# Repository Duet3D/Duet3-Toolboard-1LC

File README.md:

# Duet-3-Toolboard-1LC
Hardware information for the Duet 3 Toolboard 1LC. This is a CAN-FD connected expansion board for Duet 3 Mainboards:[Duet 3 6HC](https://www.duet3d.com/Duet3Mainboard6HC), [Duet 3 Mini 5+](https://www.duet3d.com/duet3mini5plus) or [Duet 3 6XD](https://www.duet3d.com/duet3mainboard6xd) that is designed to provide complete control for a direct drive extruder. 

Product page is here: https://www.duet3d.com/Duet3Toolboard1LC

Documentation is here: https://docs.duet3d.com/en/Duet3D_hardware/Duet_3_family/Duet_3_Toolboard_1LC

As always please discuss this on the Duet3d forum: https://forum.duet3d.com/

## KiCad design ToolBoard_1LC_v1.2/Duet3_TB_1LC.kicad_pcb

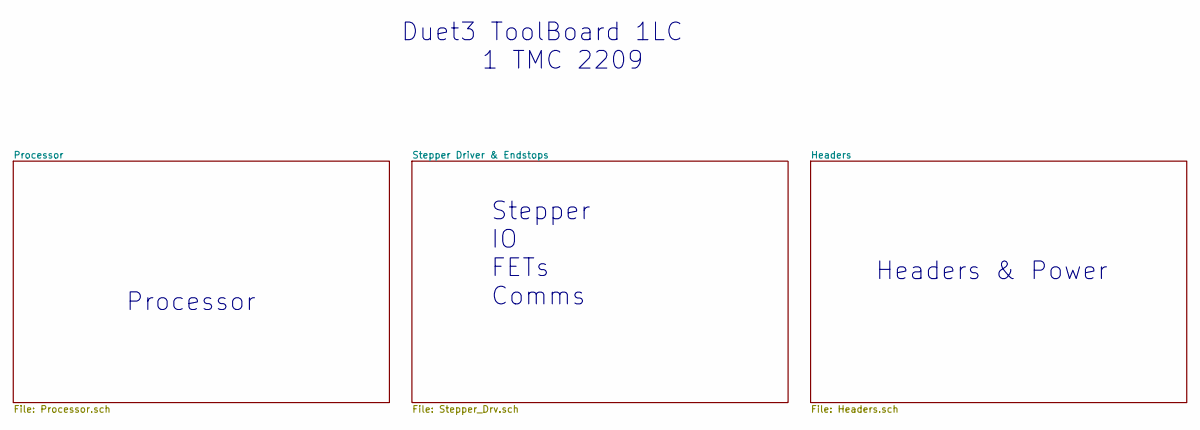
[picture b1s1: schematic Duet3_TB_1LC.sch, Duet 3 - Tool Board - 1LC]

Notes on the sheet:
Processor
Stepper IO FETs Comms
Headers & Power
Duet3 ToolBoard 1LC 1 TMC 2209

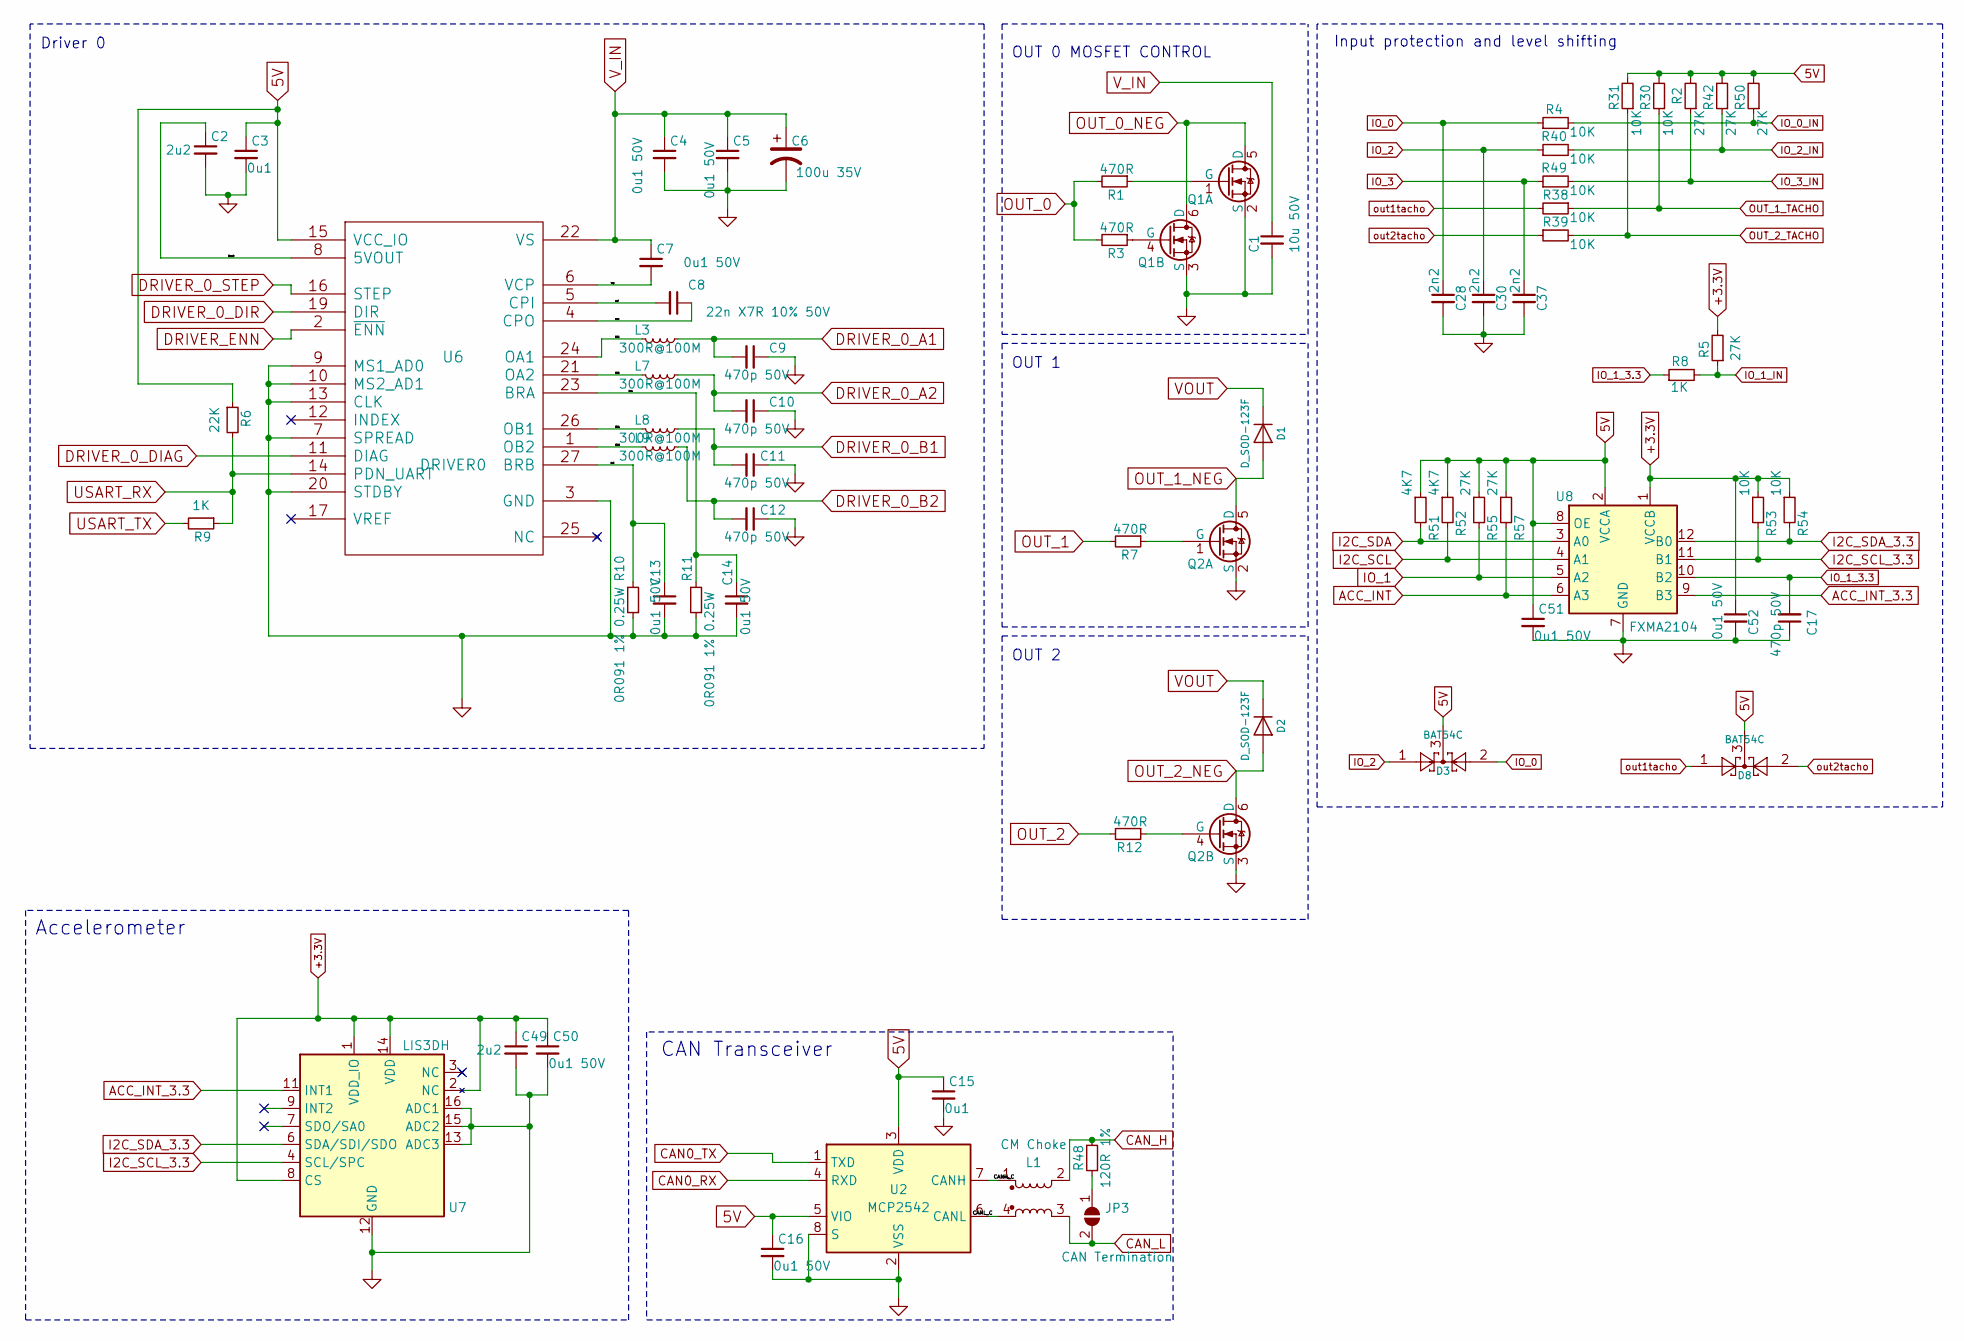
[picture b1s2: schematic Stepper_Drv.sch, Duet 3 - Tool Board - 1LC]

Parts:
C1: 10u 50V; C_1206_3216Metric; Part Number CL31A106KBHNNNE
C2, C49: 2u2; C_0603_1608Metric_Wbry; Part Number GRM188R6YA225KA12D
C3, C15: 0u1; C_0402_1005Metric_Wbry; Part Number CL05A104KA5NNNC
C4, C5, C7, C13, C14, C16, C50, C51, C52: 0u1 50V; C_0402_1005Metric_Wbry; Part Number GCM155R71H104KE02D
C6: 100u 35V; CP_Elec_6.3x7.7; Part Number 865080545012
C8: 22n X7R 10% 50V; C_0402_1005Metric_Wbry; Part Number CC0402KRX7R9BB223
C9, C10, C11, C12, C17: 470p 50V; C_0402_1005Metric_Wbry; Part Number CC0402KRX7R9BB471
C28, C30, C37: 2n2; C_0402_1005Metric_Wbry; Part Number CC0402KRX7R9BB222 or similar (10v+ is f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
D1, D2: D_SOD-123F; Part Number HS1KFL or equivalent
D3, D8: BAT54C; SOT-23; Part Number BAT54C-7-F/BAT54CLT1G
JP3: CAN Termination; SolderJumper-2_P1.3mm_Open_TrianglePad1.0x1.5mm
L1: CM Choke; Wurth_CM_Choke_744231121; Part Number 744231121 or SRF2012A-121YA
L3, L7, L8, L9: 300R@100M; L_0603_1608Metric; Part Number 742792641 or similar
Q1, Q2: Q_DUAL_NMOS; Fairchild_DualPower33-6_3x3mm-gap; Part Number DMT6018LDR
R1, R3, R7, R12: 470R; R_0402_1005Metric_Wbry; Part Number RK73H1ETTP4700F
R2, R5, R42, R50, R55, R57: 27K; R_0402_1005Metric_Wbry; Part Number RK73H1ETTP2702F
R4, R30, R31, R38, R39, R40, R49: 10K; R_0402_1005Metric_Wbry; Part Number RK73H1ETTP1002F
R6: 22K; R_0402_1005Metric_Wbry; Part Number RK73H1ETTP2202F
R8, R9: 1K; R_0402_1005Metric_Wbry; Part Number RK73H1ETTP1001F
R10, R11: 0R091 1% 0.25W; R_0402_1005Metric_Wbry; Part Number ERJ-2BWFR091X or RLP73M1ER091FTDF
R48: 120R 1%; R_0402_1005Metric_Wbry; Part Number RMCF0402FT120R
R51, R52: 4K7; R_0402_1005Metric_Wbry; Part Number RK73H1ETTP4701F
R53, R54: 10K; R_0402_1005Metric_Wbry; Part Number RK73H1ETTP4701F
U2: MCP2542; DFN-8-1EP_3x2mm_P0.5mm_EP1.3x1.5mm-thinpads; Part Number MCP2542, alternitivelty MCP2558
U6: DRIVER0; QFN-28-1EP_5x5mm_Pitch0.5mm-thinpads; Part Number TMC2209
U7: LIS3DH; Part Number LIS3DHTR
U8: FXMA2104; UMLP-12-1.8x1.8mm_P0.4mm

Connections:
5V: C3.1, C15.1, C16.1, C51.1, D3.3, D8.3, R2.2, R6.1, R30.2, R31.2, R42.2, R50.2, R51.1, R52.1, R55.1, R57.1, U2.3 (VDD), U2.5 (VIO), U6.15 (VCC_IO), U8.2 (VCCA), U8.8 (OE); also elsewhere on the board
+3.3V: C49.1, C50.1, C52.1, R5.2, R53.1, R54.1, U7.1 (VDD_IO), U7.2 (NC), U7.8 (CS), U7.14 (VDD), U8.1 (VCCB); also elsewhere on the board
/Stepper Driver & Endstops/5vout: C2.1, U6.8 (5VOUT)
/Stepper Driver & Endstops/CANH_C: L1.1, U2.7 (CANH)
/Stepper Driver & Endstops/CANL_C: L1.4, U2.6 (CANL)
/Stepper Driver & Endstops/OA1: L3.2, U6.24 (OA1)
/Stepper Driver & Endstops/OA2: L7.2, U6.21 (OA2)
/Stepper Driver & Endstops/OB1: L8.2, U6.26 (OB1)
/Stepper Driver & Endstops/OB2: L9.2, U6.1 (OB2)
/Stepper Driver & Endstops/bra: C14.1, R11.2, U6.23 (BRA)
/Stepper Driver & Endstops/brb: C13.1, R10.2, U6.27 (BRB)
/Stepper Driver & Endstops/cpi: C8.2, U6.5 (CPI)
/Stepper Driver & Endstops/cpo: C8.1, U6.4 (CPO)
/Stepper Driver & Endstops/vcp: C7.2, U6.6 (VCP)
ACC_INT: R57.2, U8.6 (A3); also elsewhere on the board
ACC_INT_3.3: U7.11 (INT1), U8.9 (B3)
CAN0_RX: U2.4 (RXD); also elsewhere on the board
CAN0_TX: U2.1 (TXD); also elsewhere on the board
CAN_H: L1.2, R48.2; also elsewhere on the board
CAN_L: JP3.2 (B), L1.3; also elsewhere on the board
DRIVER_0_A1: C9.2, L3.1; also elsewhere on the board
DRIVER_0_A2: C10.2, L7.1; also elsewhere on the board
DRIVER_0_B1: C11.2, L8.1; also elsewhere on the board
DRIVER_0_B2: C12.2, L9.1; also elsewhere on the board
DRIVER_0_DIAG: U6.11 (DIAG); also elsewhere on the board
DRIVER_0_DIR: U6.19 (DIR); also elsewhere on the board
DRIVER_0_STEP: U6.16 (STEP); also elsewhere on the board
DRIVER_ENN: U6.2 (~ENN); also elsewhere on the board
GND: C1.2, C2.2, C3.2, C4.2, C5.2, C6.2, C9.1, C10.1, C11.1, C12.1, C13.2, C14.2, C15.2, C16.2, C17.1, C28.2, C30.2, C37.2, C49.2, C50.2, C51.2, C52.2, Q1.2 (S), Q1.3 (S), Q2.2 (S), Q2.3 (S), R10.1, R11.1, U2.2 (VSS), U2.8 (S), U2.9 (VSS), U6.3 (GND), U6.7 (SPREAD), U6.9 (MS1_AD0), U6.10 (MS2_AD1), U6.13 (CLK), U6.18 (GND), U6.20 (STDBY), U6.29 (GND), U7.5 (GND), U7.10 (GND), U7.12 (GND), U7.13 (ADC3), U7.15 (ADC2), U7.16 (ADC1), U8.7 (GND); also elsewhere on the board
I2C_SCL: R52.2, U8.4 (A1); also elsewhere on the board
I2C_SCL_3.3: R53.2, U7.4 (SCL/SPC), U8.11 (B1)
I2C_SDA: R51.2, U8.3 (A0); also elsewhere on the board
I2C_SDA_3.3: R54.2, U7.6 (SDA/SDI/SDO), U8.12 (B0)
IO_0: C28.1, D3.2, R4.1; also elsewhere on the board
IO_0_IN: R4.2, R50.1; also elsewhere on the board
IO_1: R55.2, U8.5 (A2); also elsewhere on the board
IO_1_3.3: C17.2, R8.1, U8.10 (B2)
IO_1_IN: R5.1, R8.2; also elsewhere on the board
IO_2: C30.1, D3.1, R40.1; also elsewhere on the board
IO_2_IN: R40.2, R42.1; also elsewhere on the board
IO_3: C37.1, R49.1; also elsewhere on the board
IO_3_IN: R2.1, R49.2; also elsewhere on the board
unnamed: JP3.1 (A), R48.1
unnamed: Q1.1 (G), R1.1
unnamed: Q1.4 (G), R3.1
unnamed: Q2.1 (G), R7.1
unnamed: Q2.4 (G), R12.1
OUT_0: R1.2, R3.2; also elsewhere on the board
OUT_0_NEG: Q1.5 (D), Q1.6 (D); also elsewhere on the board
OUT_1: R7.2; also elsewhere on the board
OUT_1_NEG: D1.2 (A), Q2.5 (D); also elsewhere on the board
OUT_1_TACHO: R30.1, R38.1; also elsewhere on the board
OUT_2: R12.2; also elsewhere on the board
OUT_2_NEG: D2.2 (A), Q2.6 (D); also elsewhere on the board
OUT_2_TACHO: R31.1, R39.2; also elsewhere on the board
USART_RX: R6.2, R9.1, U6.14 (PDN_UART); also elsewhere on the board
USART_TX: R9.2; also elsewhere on the board
VOUT: D1.1 (K), D2.1 (K); also elsewhere on the board
V_IN: C1.1, C4.1, C5.1, C6.1, C7.1, U6.22 (VS), U6.28 (VS); also elsewhere on the board
out1tacho: D8.1, R38.2; also elsewhere on the board
out2tacho: D8.2, R39.1; also elsewhere on the board

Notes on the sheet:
Input protection and level shifting
Driver 0
OUT 1
OUT 0 MOSFET CONTROL
CAN Transceiver
OUT 2
Accelerometer

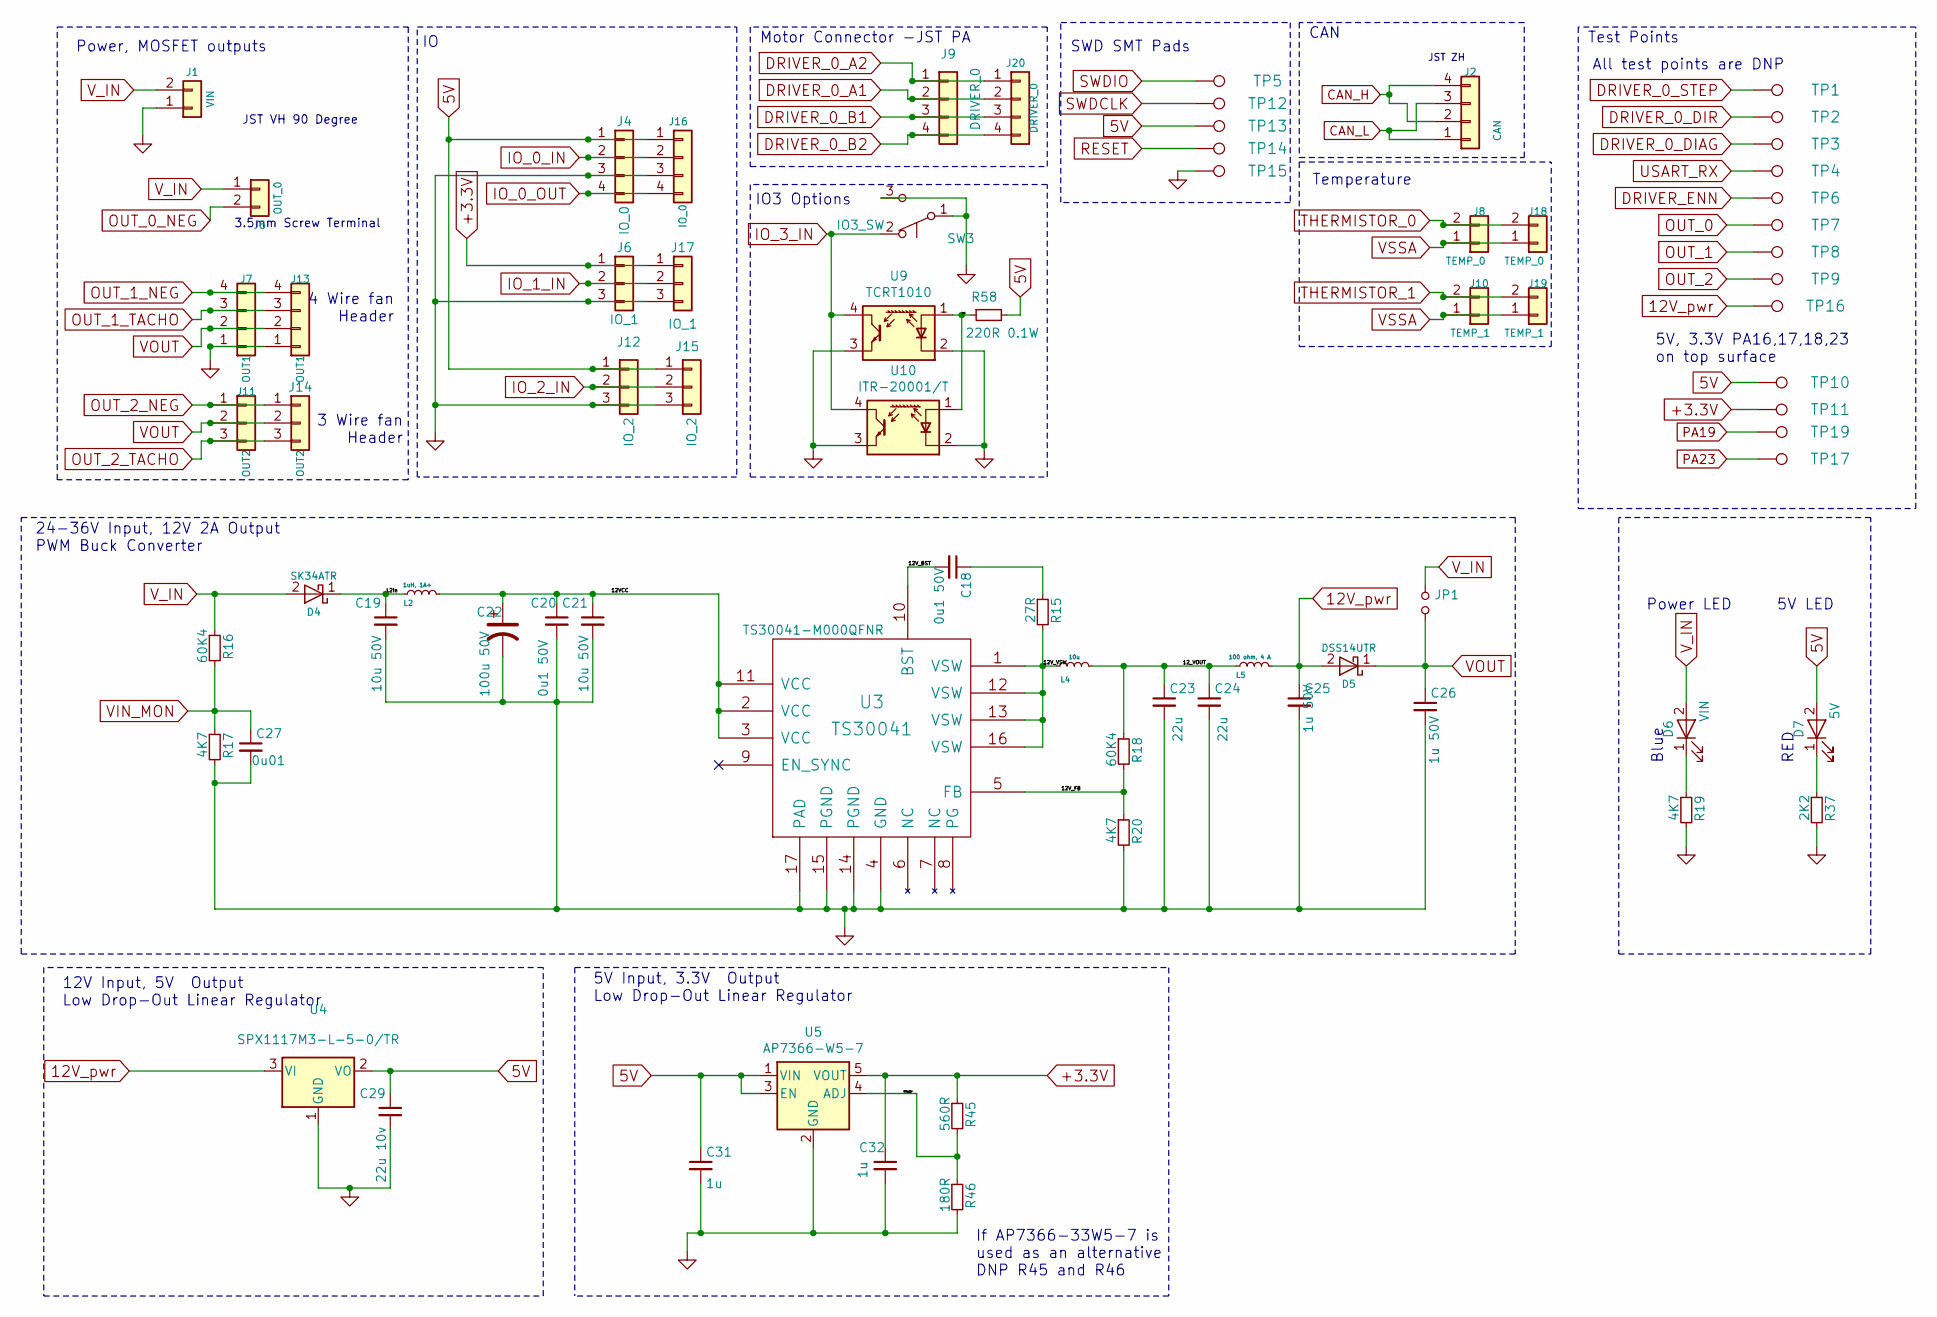
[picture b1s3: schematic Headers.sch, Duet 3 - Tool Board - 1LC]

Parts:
C18: 0u1 50V; C_0402_1005Metric_Wbry; Part Number CL05A104KA5NNNC
C19, C21: 10u 50V; C_1206_3216Metric; Part Number CL31A106KBHNNNE
C20: 0u1 50V; C_0402_1005Metric_Wbry; Part Number GRM155R61H104JE14D
C22: 100u 50V; CP_Elec_6.3x7.7; Part Number EEE-FTH101XAP
C23, C24: 22u; C_0805_2012Metric; Rating 25V; Part Number GRM21BR61E226ME44L
C25, C26: 1u 50V; C_0603_1608Metric_Wbry; Part Number CL10A105KB8NNNC
C27: 0u01; C_0402_1005Metric_Wbry; Part Number TMK105B7103KV-F
C29: 22u 10v; C_0805_2012Metric; Part Number GRM21BR61A226ME51L or equivalent
C31, C32: 1u; C_0603_1608Metric_Wbry; Part Number CL10A105KA8NNNC
D4: SK34ATR; D_SMA; Rating 1A+ 40V+; Part Number SK34ATR or similar SMA footprint
D5: DSS14UTR; D_SOD-123F; Rating 1A,40V; Part Number DSS14UTR or RB162MM-40TR or similar
D6: VIN; LED_0603_1608Metric; Part Number 150060BS75000 or equivalent Blue
D7: 5V; LED_0603_1608Metric; Part Number 150060RS75000 or equivalent Red
J1: VIN; JST_VH_B2PS-VH_1x02_P3.96mm_Short_Horizontal; Part Number B2PS-VH(LF)(SN)
J2: CAN; JST_ZH_S4B-ZH_1x04_P1.50mm_Horizontal; Part Number S4B-ZR(LF)(SN)
J4: IO_0; JST_PH_S4B-PH-K_1x04_P2.00mm_Horizontal; Part Number S4B-PH-K-S(LF)(SN)
J5: OUT_0; 3.5MM_2X1; Part Number Kaifeng KF128L-3.50-2
J6: IO_1; JST_PH_S3B-PH-K_1x03_P2.00mm_Horizontal; Part Number S3B-PH-K-S(LF)(SN)
J7: OUT1; JST_PH_S4B-PH-K_1x04_P2.00mm_Horizontal; Part Number S4B-PH-K-S(LF)(SN)
J8: TEMP_0; JST_PH_S2B-PH-K_1x02_P2.00mm_Horizontal; Part Number S2B-PH-K-S(LF)(SN)
J9: DRIVER_0; JST_PH_S4B-PH-K_1x04_P2.00mm_Horizontal; Part Number S4B-PH-K-S(LF)(SN)
J10: TEMP_1; JST_PH_S2B-PH-K_1x02_P2.00mm_Horizontal; Part Number S2B-PH-K-S(LF)(SN)
J11: OUT2; JST_PH_S3B-PH-K_1x03_P2.00mm_Horizontal; Part Number S3B-PH-K-S(LF)(SN)
J12: IO_2; JST_PH_S3B-PH-K_1x03_P2.00mm_Horizontal; Part Number S3B-PH-K-S(LF)(SN)
J13: OUT1; TerminalBlock_TE_282834-4_1x04_P2.54mm_Horizontal; Part Number - DNP
J14: OUT2; TerminalBlock_TE_282834-3_1x03_P2.54mm_Horizontal; Part Number - DNP
J15: IO_2; TerminalBlock_TE_282834-3_1x03_P2.54mm_Horizontal; Part Number DNP
J16: IO_0; TerminalBlock_TE_282834-4_1x04_P2.54mm_Horizontal; Part Number - DNP
J17: IO_1; TerminalBlock_TE_282834-3_1x03_P2.54mm_Horizontal; Part Number - DNP
J18: TEMP_0; TerminalBlock_Valcon_MB312-2.54-02_P2.54mm_Horizontal; Part Number MB312-2.54-02_P2.54mm - DNP
J19: TEMP_1; TerminalBlock_Valcon_MB312-2.54-02_P2.54mm_Horizontal; Part Number MB312-2.54-02_P2.54mm - DNP
J20: DRIVER_0; TerminalBlock_TE_282834-4_1x04_P2.54mm_Horizontal; Part Number - DNP
JP1: V_OUT JMP; PinHeader_1x02_P2.54mm_Vertical
L2: 1uH, 1A+; L_1008_2512Metric; Part Number MGV2520101R0M-10 or similar 1008 footpr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
L4: 10u; L_Wuerth_7440405xxxx; Part Number 74404054100 or NR5040T100M
L5: 100 ohm, 4 A; L_0805_2012Metric; Part Number MPZ2012S101A or similar
R15: 27R; R_0402_1005Metric_Wbry; Rating 0.1W+; Part Number RC0402FR-0727RL
R16, R18: 60K4; R_0402_1005Metric_Wbry; Part Number ERJ-2RKF6042X
R17, R19, R20: 4K7; R_0402_1005Metric_Wbry; Part Number RK73H1ETTP4701F
R37: 2K2; R_0402_1005Metric_Wbry; Part Number RK73H1ETTP2201F
R45: 560R; R_0402_1005Metric_Wbry; Part Number RMCF0402FT560R
R46: 180R; R_0402_1005Metric_Wbry; Part Number RMCF0402FT180R
R58: 220R 0.1W; R_0402_1005Metric_Wbry; Part Number RK73H1ETTP2200F
SW3: IO3_SW; Ultra_Subminiature_Switch-SPDT; Part Number DNP - Omron D2FD-1L30-1T
TP1: STEP; TestPoint_Pad_D1.5mm; Part Number virtual component - DNP
TP2: DIR; TestPoint_Pad_D1.5mm; Part Number virtual component - DNP
TP3: DIAG; TestPoint_Pad_D1.5mm; Part Number virtual component - DNP
TP4: U_RX; TestPoint_Pad_D1.5mm; Part Number virtual component - DNP
TP5: SWDIO; TestPoint_Pad_D1.5mm; Part Number virtual component - DNP
TP6: ENN; TestPoint_Pad_D1.5mm; Part Number virtual component - DNP
TP7: OUT_0; TestPoint_Pad_D1.5mm; Part Number virtual component - DNP
TP8: OUT_1; TestPoint_Pad_D1.5mm; Part Number virtual component - DNP
TP9: OUT_2; TestPoint_Pad_D1.5mm; Part Number virtual component - DNP
TP10, TP13: 5V; TestPoint_Pad_D1.5mm; Part Number virtual component - DNP
TP11: 3.3V; TestPoint_Pad_D1.5mm; Part Number virtual component - DNP
TP12: SWDCLK; TestPoint_Pad_D1.5mm; Part Number virtual component - DNP
TP14: RESET; TestPoint_Pad_D1.5mm; Part Number virtual component - DNP
TP15: GND; TestPoint_Pad_D1.5mm; Part Number virtual component - DNP
TP16: 12V_pwr; TestPoint_Pad_D1.5mm; Part Number virtual component - DNP
TP17: PA23; TestPoint_Pad_D1.5mm; Part Number virtual component - DNP
TP19: PA19; TestPoint_Pad_D1.5mm; Part Number virtual component - DNP
U3: TS30041; QFN-16-1EP_3x3mm_P0.5mm_EP1.8x1.8mm-thinpads; Rating Adj (set to 12V) 1A; Part Number TS30041-M000QFNR
U4: SPX1117M3-L-5-0/TR; SOT-223-3_TabPin2; Part Number SPX1117M3-L-5-0/TR
U5: AP7366-W5-7; SOT-23-5; Part Number AP7366-W5-7 (If AP7366-33W5-7 is used a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
U9: TCRT1010; Vishay_TCRT1010; Part Number DNP
U10: ITR-20001/T; ITR-20001_T; Part Number DNP

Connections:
5V: C29.1, C31.1, D7.2 (A), J4.1, J12.1, J15.1, J16.1, R58.2, TP10.1, TP13.1, U4.2 (VO), U5.1 (VIN), U5.3 (EN); also elsewhere on the board
12V_pwr: C25.1, D5.2 (A), L5.2, TP16.1, U4.3 (VI)
+3.3V: C32.1, J6.1, J17.1, R45.1, TP11.1, U5.5 (VOUT); also elsewhere on the board
/Headers/3V3_ADJ: R45.2, R46.1, U5.4 (ADJ)
/Headers/12VCC: C20.1, C21.1, C22.1, L2.2, U3.2 (VCC), U3.3 (VCC), U3.11 (VCC)
/Headers/12V_BST: C18.2, U3.10 (BST)
/Headers/12V_FB: R18.2, R20.1, U3.5 (FB)
/Headers/12V_VSW: L4.1, R15.2, U3.1 (VSW), U3.12 (VSW), U3.13 (VSW), U3.16 (VSW)
/Headers/12_VOUT: C23.1, C24.1, L4.2, L5.1, R18.1
/Headers/L2in: C19.1, D4.1 (K), L2.1
/Headers/col: R58.1, U9.1 (A), U10.1 (A)
CAN_H: J2.2, J2.4; also elsewhere on the board
CAN_L: J2.1, J2.3; also elsewhere on the board
DRIVER_0_A1: J9.2, J20.2; also elsewhere on the board
DRIVER_0_A2: J9.1, J20.1; also elsewhere on the board
DRIVER_0_B1: J9.3, J20.3; also elsewhere on the board
DRIVER_0_B2: J9.4, J20.4; also elsewhere on the board
DRIVER_0_DIAG: TP3.1; also elsewhere on the board
DRIVER_0_DIR: TP2.1; also elsewhere on the board
DRIVER_0_STEP: TP1.1; also elsewhere on the board
DRIVER_ENN: TP6.1; also elsewhere on the board
GND: C19.2, C20.2, C21.2, C22.2, C23.2, C24.2, C25.2, C26.2, C27.2, C29.2, C31.2, C32.2, J1.1, J4.3, J6.3, J7.1, J12.3, J13.1, J15.3, J16.3, J17.3, R17.2, R19.2, R20.2, R37.2, R46.2, SW3.1 (B), SW3.3 (C), TP15.1, U3.4 (GND), U3.14 (PGND), U3.15 (PGND), U3.17 (PAD), U4.1 (GND), U5.2 (GND), U9.2 (K), U9.3 (E), U10.2 (K), U10.3 (E); also elsewhere on the board
IO_0_IN: J4.2, J16.2; also elsewhere on the board
IO_0_OUT: J4.4, J16.4; also elsewhere on the board
IO_1_IN: J6.2, J17.2; also elsewhere on the board
IO_2_IN: J12.2, J15.2; also elsewhere on the board
IO_3_IN: SW3.2 (A), U9.4 (C), U10.4 (C); also elsewhere on the board
unnamed: C18.1, R15.1
unnamed: D6.1 (K), R19.1
unnamed: D7.1 (K), R37.1
OUT_0: TP7.1; also elsewhere on the board
OUT_0_NEG: J5.2; also elsewhere on the board
OUT_1: TP8.1; also elsewhere on the board
OUT_1_NEG: J7.4, J13.4; also elsewhere on the board
OUT_1_TACHO: J7.3, J13.3; also elsewhere on the board
OUT_2: TP9.1; also elsewhere on the board
OUT_2_NEG: J11.1, J14.1; also elsewhere on the board
OUT_2_TACHO: J11.3, J14.3; also elsewhere on the board
PA19: TP19.1; also elsewhere on the board
PA23: TP17.1; also elsewhere on the board
RESET: TP14.1; also elsewhere on the board
SWDCLK: TP12.1; also elsewhere on the board
SWDIO: TP5.1; also elsewhere on the board
THERMISTOR_0: J8.2, J18.2; also elsewhere on the board
THERMISTOR_1: J10.2, J19.2; also elsewhere on the board
USART_RX: TP4.1; also elsewhere on the board
VIN_MON: C27.1, R16.2, R17.1; also elsewhere on the board
VOUT: C26.1, D5.1 (K), J7.2, J11.2, J13.2, J14.2, JP1.2; also elsewhere on the board
VSSA: J8.1, J10.1, J18.1, J19.1; also elsewhere on the board
V_IN: D4.2 (A), D6.2 (A), J1.2, J5.1, JP1.1, R16.1; also elsewhere on the board

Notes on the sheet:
Power, MOSFET outputs
Temperature
Motor Connector -JST PA
Test Points
All test points are DNP
CAN
SWD SMT Pads
4 Wire fan Header
5V, 3.3V PA16,17,18,23 on top surface
5V Input, 3.3V Output Low Drop-Out Linear Regulator
Power LED
Blue
12V Input, 5V Output Low Drop-Out Linear Regulator
24-36V Input, 12V 2A Output PWM Buck Converter
3.5mm Screw Terminal
3 Wire fan Header
5V LED
RED
JST VH 90 Degree
JST ZH
IO3 Options
If AP7366-33W5-7 is used as an alternative DNP R45 and R46

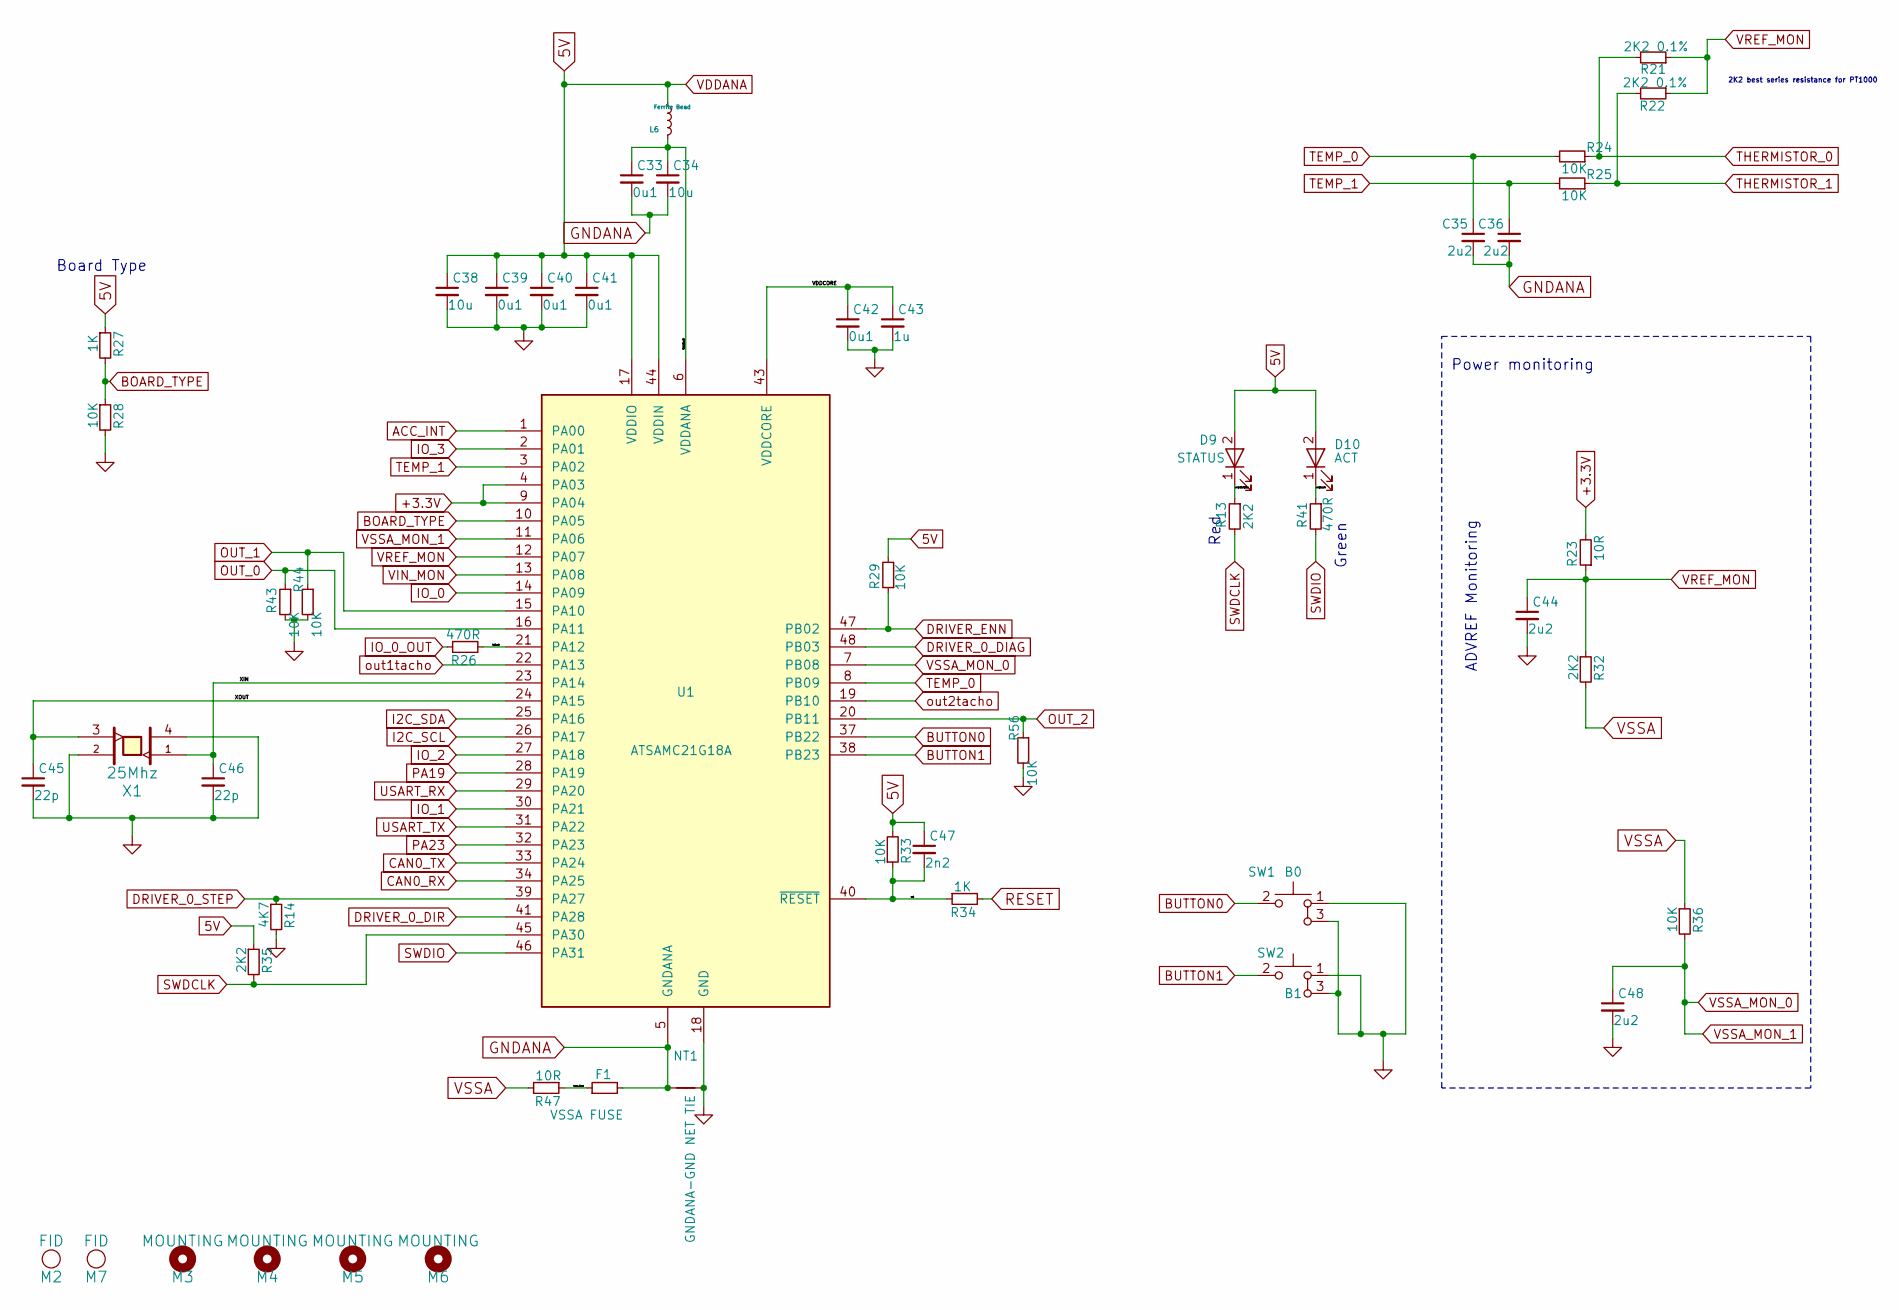
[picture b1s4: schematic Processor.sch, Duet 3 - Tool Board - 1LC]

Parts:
C33, C39, C40, C41, C42: 0u1; C_0402_1005Metric_Wbry; Part Number CL05A104KA5NNNC
C34, C38: 10u; C_0805_2012Metric; Part Number CL21A106KPFNNNG
C35, C36, C44, C48: 2u2; C_0603_1608Metric_Wbry; Part Number GRM188R6YA225KA12D
C43: 1u; C_0603_1608Metric_Wbry; Part Number CL10A105KA8NNNC
C45, C46: 22p; C_0402_1005Metric_Wbry; Part Number C0402C220J4GACTU
C47: 2n2; C_0402_1005Metric_Wbry; Part Number CC0402KRX7R9BB222 or similar (10v+ is f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
D9: STATUS; LED_0603_1608Metric; Part Number 150060RS75000 or equivalent Red
D10: ACT; LED_0603_1608Metric; Part Number 150060VS75000 or equivalent Green
F1: VSSA FUSE; Fuse_1206_3216Metric; Part Number 0ZCJ0020FF2E
L6: Ferrite Bead; L_0402_1005Metric; Part Number BKP1005HS221-T
M2, M7: FID; Fiducial_1mm_Mask2mm; Part Number virtual component - DNP
M3, M4, M5, M6: MOUNTING; MountingHole_3.2mm_M3; Part Number virtual component - DNP
NT1: GNDANA-GND NET TIE; NetTie-2_SMD_Pad0.5mm; Part Number virtual component - DNP
R13, R32, R35: 2K2; R_0402_1005Metric_Wbry; Part Number RK73H1ETTP2201F
R14: 4K7; R_0402_1005Metric_Wbry; Part Number RK73H1ETTP4701F
R21, R22: 2K2 0.1%; R_0402_1005Metric_Wbry; Part Number RT0402BRE072K2L
R23, R47: 10R; R_0402_1005Metric_Wbry; Part Number RK73H1ETTP10R0F
R24, R25, R29, R33, R36, R43, R44, R56: 10K; R_0402_1005Metric_Wbry; Part Number RK73H1ETTP1002F
R26, R41: 470R; R_0402_1005Metric_Wbry; Part Number RK73H1ETTP4700F
R27: 1K; R_0402_1005Metric_Wbry; Part Number RK73H1ETTP2202F
R28: 10K; R_0402_1005Metric_Wbry; Part Number RK73H1ETTP1001F
R34: 1K; R_0402_1005Metric_Wbry; Part Number RK73H1ETTP1001F
SW1: B0; SW_TL3340AF160QG; Part Number TL3340AF160QG
SW2: B1; SW_TL3340AF160QG; Part Number TL3340AF160QG
U1: ATSAMC21G18A; QFN-48-1EP_7x7mm_P0.5mm_EP5.2x5.2mm_ThermalVias_thinpads; Part Number ATSAMC21G18A
X1: TSX-3225 25.0000MF10P; Crystal_SMD_ECS-33B-4Pin_3.2x2.5mm; Part Number TSX-3225 25.0000MF10P

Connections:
5V: C38.1, C39.1, C40.1, C41.1, C47.1, D9.2 (A), D10.2 (A), L6.1, R27.1, R29.2, R33.2, R35.1, U1.17 (VDDIO), U1.36 (VDDIO), U1.44 (VDDIN); also elsewhere on the board
+3.3V: R23.2, U1.4 (PA03), U1.9 (PA04); also elsewhere on the board
/Processor/VDDANA_IN: C33.1, C34.1, L6.2, U1.6 (VDDANA)
/Processor/VDDCORE: C42.1, C43.1, U1.43 (VDDCORE)
/Processor/XIN: C46.1, U1.23 (PA14), X1.1
/Processor/XOUT: C45.1, U1.24 (PA15), X1.3
/Processor/io0out: R26.2, U1.21 (PA12)
/Processor/rst: C47.2, R33.1, R34.1, U1.40 (~RESET)
/Processor/swdclkstatus: D9.1 (K), R13.1
/Processor/swdioact: D10.1 (K), R41.1
/Processor/vssa_fuse: F1.1, R47.1
ACC_INT: U1.1 (PA00); also elsewhere on the board
BOARD_TYPE: R27.2, R28.1, U1.10 (PA05)
BUTTON0: SW1.2, U1.37 (PB22)
BUTTON1: SW2.2, U1.38 (PB23)
CAN0_RX: U1.34 (PA25); also elsewhere on the board
CAN0_TX: U1.33 (PA24); also elsewhere on the board
DRIVER_0_DIAG: U1.48 (PB03); also elsewhere on the board
DRIVER_0_DIR: U1.41 (PA28); also elsewhere on the board
DRIVER_0_STEP: R14.1, U1.39 (PA27); also elsewhere on the board
DRIVER_ENN: R29.1, U1.47 (PB02); also elsewhere on the board
GND: C38.2, C39.2, C40.2, C41.2, C42.2, C43.2, C44.2, C45.2, C46.2, C48.2, NT1.2, R14.2, R28.2, R43.2, R44.2, R56.2, SW1.1, SW1.3, SW2.1, SW2.3, U1.18 (GND), U1.35 (GND), U1.42 (GND), U1.49 (GND), X1.2, X1.4; also elsewhere on the board
GNDANA: C33.2, C34.2, C35.2, C36.2, F1.2, NT1.1, U1.5 (GNDANA)
I2C_SCL: U1.26 (PA17); also elsewhere on the board
I2C_SDA: U1.25 (PA16); also elsewhere on the board
IO_0: U1.14 (PA09); also elsewhere on the board
IO_0_OUT: R26.1; also elsewhere on the board
IO_1: U1.30 (PA21); also elsewhere on the board
IO_2: U1.27 (PA18); also elsewhere on the board
IO_3: U1.2 (PA01); also elsewhere on the board
OUT_0: R43.1, U1.16 (PA11); also elsewhere on the board
OUT_1: R44.1, U1.15 (PA10); also elsewhere on the board
OUT_2: R56.1, U1.20 (PB11); also elsewhere on the board
PA19: U1.28 (PA19); also elsewhere on the board
PA23: U1.32 (PA23); also elsewhere on the board
RESET: R34.2; also elsewhere on the board
SWDCLK: R13.2, R35.2, U1.45 (PA30); also elsewhere on the board
SWDIO: R41.2, U1.46 (PA31); also elsewhere on the board
TEMP_0: C35.1, R24.2, U1.8 (PB09)
TEMP_1: C36.1, R25.2, U1.3 (PA02)
THERMISTOR_0: R21.2, R24.1; also elsewhere on the board
THERMISTOR_1: R22.2, R25.1; also elsewhere on the board
USART_RX: U1.29 (PA20); also elsewhere on the board
USART_TX: U1.31 (PA22); also elsewhere on the board
VIN_MON: U1.13 (PA08); also elsewhere on the board
VREF_MON: C44.1, R21.1, R22.1, R23.1, R32.1, U1.12 (PA07)
VSSA: R32.2, R36.1, R47.2; also elsewhere on the board
VSSA_MON_0: C48.1, R36.2, U1.7 (PB08), U1.11 (PA06)
out1tacho: U1.22 (PA13); also elsewhere on the board
out2tacho: U1.19 (PB10); also elsewhere on the board

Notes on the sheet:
2K2 best series resistance for PT1000
Power monitoring
Board Type
ADVREF Monitoring
Red
Green

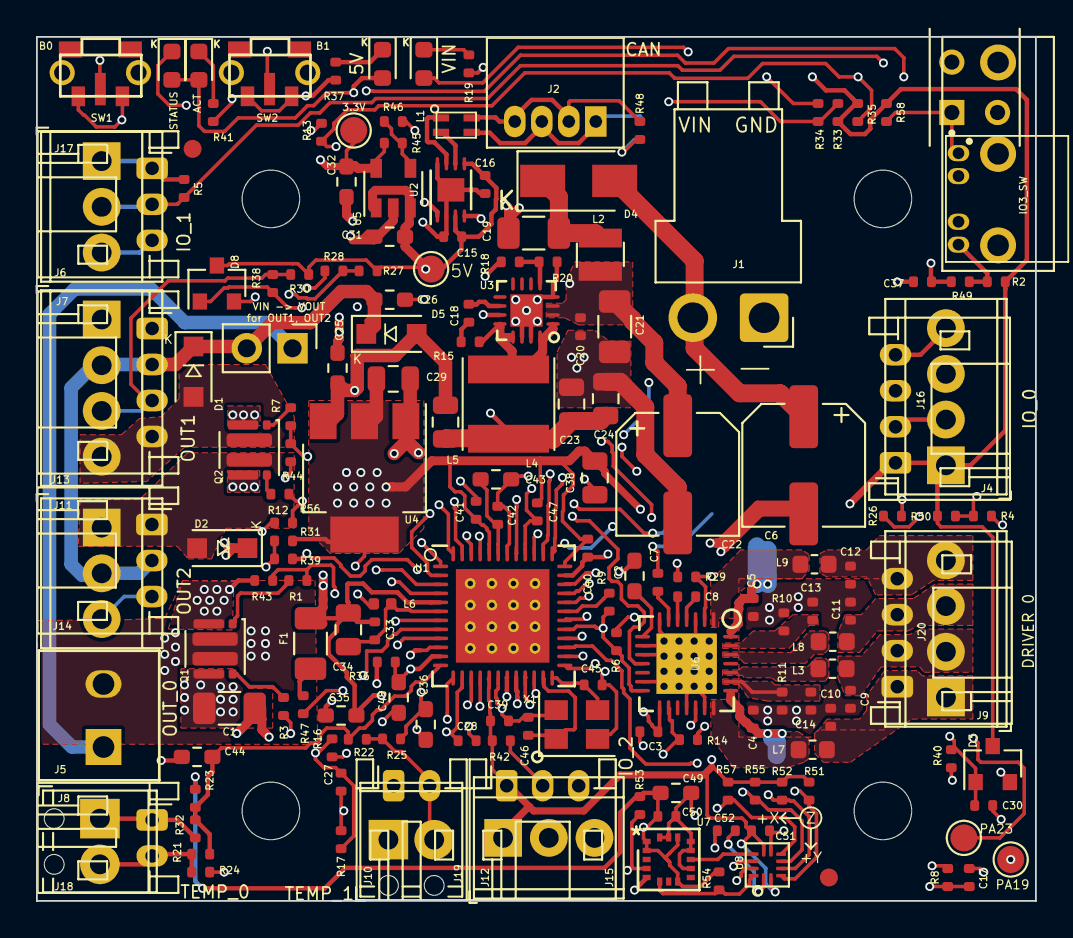
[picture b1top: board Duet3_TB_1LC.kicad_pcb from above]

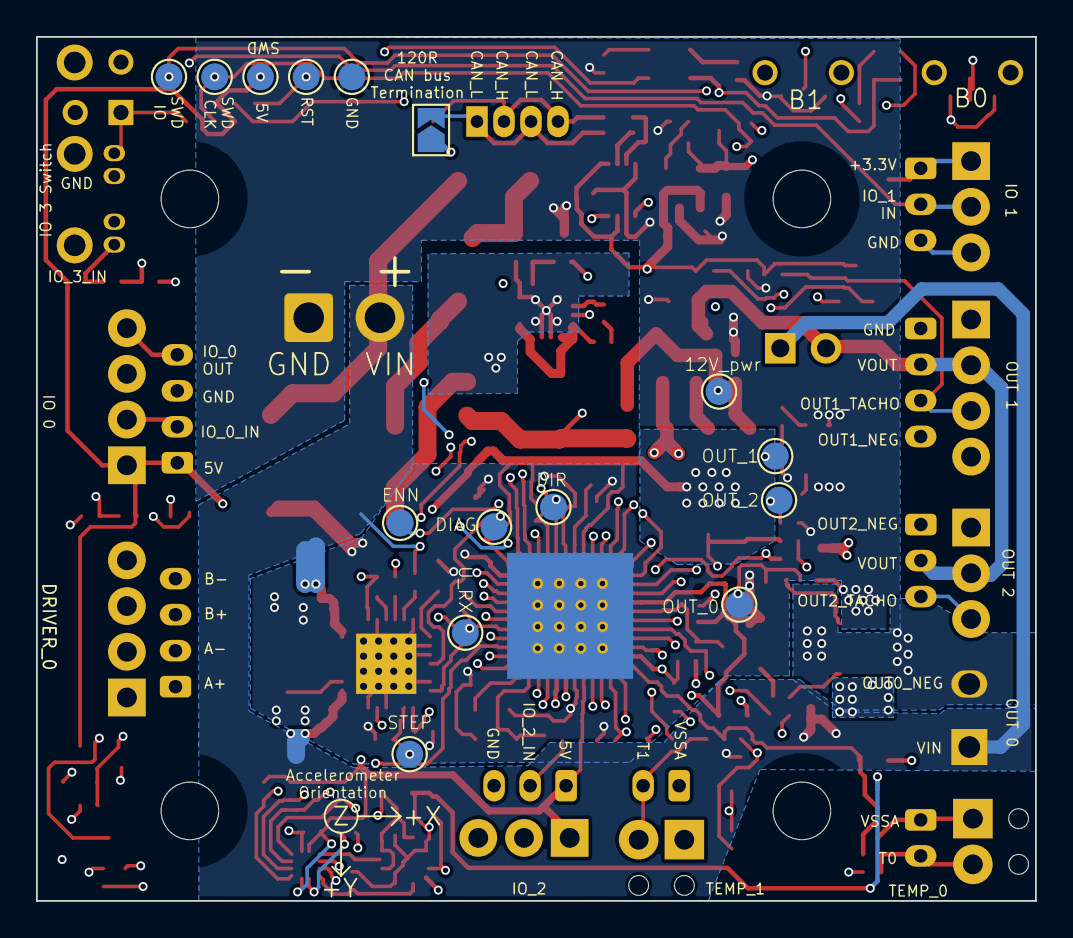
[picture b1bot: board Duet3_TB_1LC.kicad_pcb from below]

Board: 4 copper layers, 55.5 x 48.0 mm, 192 parts (15 on the bottom side), 100 nets.

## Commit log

2020-02-28 ToolBoard_1LC_v0.6 Schematic and Step file added
2020-02-28 added image and description
2020-06-15 Added wiring and dimension .svgs
2020-06-15 Added Toolboard v1.0 schematic, step and documentation svgs
2020-06-15 Update Duet3_TB_1LC_v1.0_Wiring_Diagram.svg
    Fixed labelling error on temp 1
2020-11-08 Added iboms
    also removed v1.0 files that were incorrectly in v0.6 directory
2021-05-02 Added step file for v1.1
2021-05-06 Update Duet3_TB_1LC_v1.1_STEP.zip
    Added diode to back of the board
2021-06-23 Added schematic
2021-06-23 Renamed v1.1 schematic
2021-11-10 added v1.2 step
2021-12-21 KiCad files for v0.6
2021-12-21 KiCad files for v1.0
2021-12-21 KiCAD files for v1.1
2021-12-21 Toolboard v1.2 source files.
2021-12-23 Add Duet 3 License
2022-02-15 Update Duet3_TB_1LC_Schematic_v1.1.pdf
    Incorrect version loaded originally.
2022-03-09 v1.2 STEP
2022-05-30 Added iBOM, Schematic and STEP for Toolboard v1.3
2023-11-30 typo

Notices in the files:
ToolBoard_1LC_v0.6/Duet3_TB_1LC.sch:
License: CERN OHL v1.2
